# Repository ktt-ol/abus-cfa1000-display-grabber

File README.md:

# ABUS CFA1000 Display Grabber

This project's aim is accessing information from the ABUS CFA1000,
that are only shown on its display. For this task the display is
removed and the display pins are connected to a custom PCB developed
in this repository.

You can find more details here:

https://www.mainframe.io/project/abus-cfa1000-display-grabber.html

The PCB has been developed with KiCAD 4.0, which is available from
kicad-pcb.org for all major operating systems.

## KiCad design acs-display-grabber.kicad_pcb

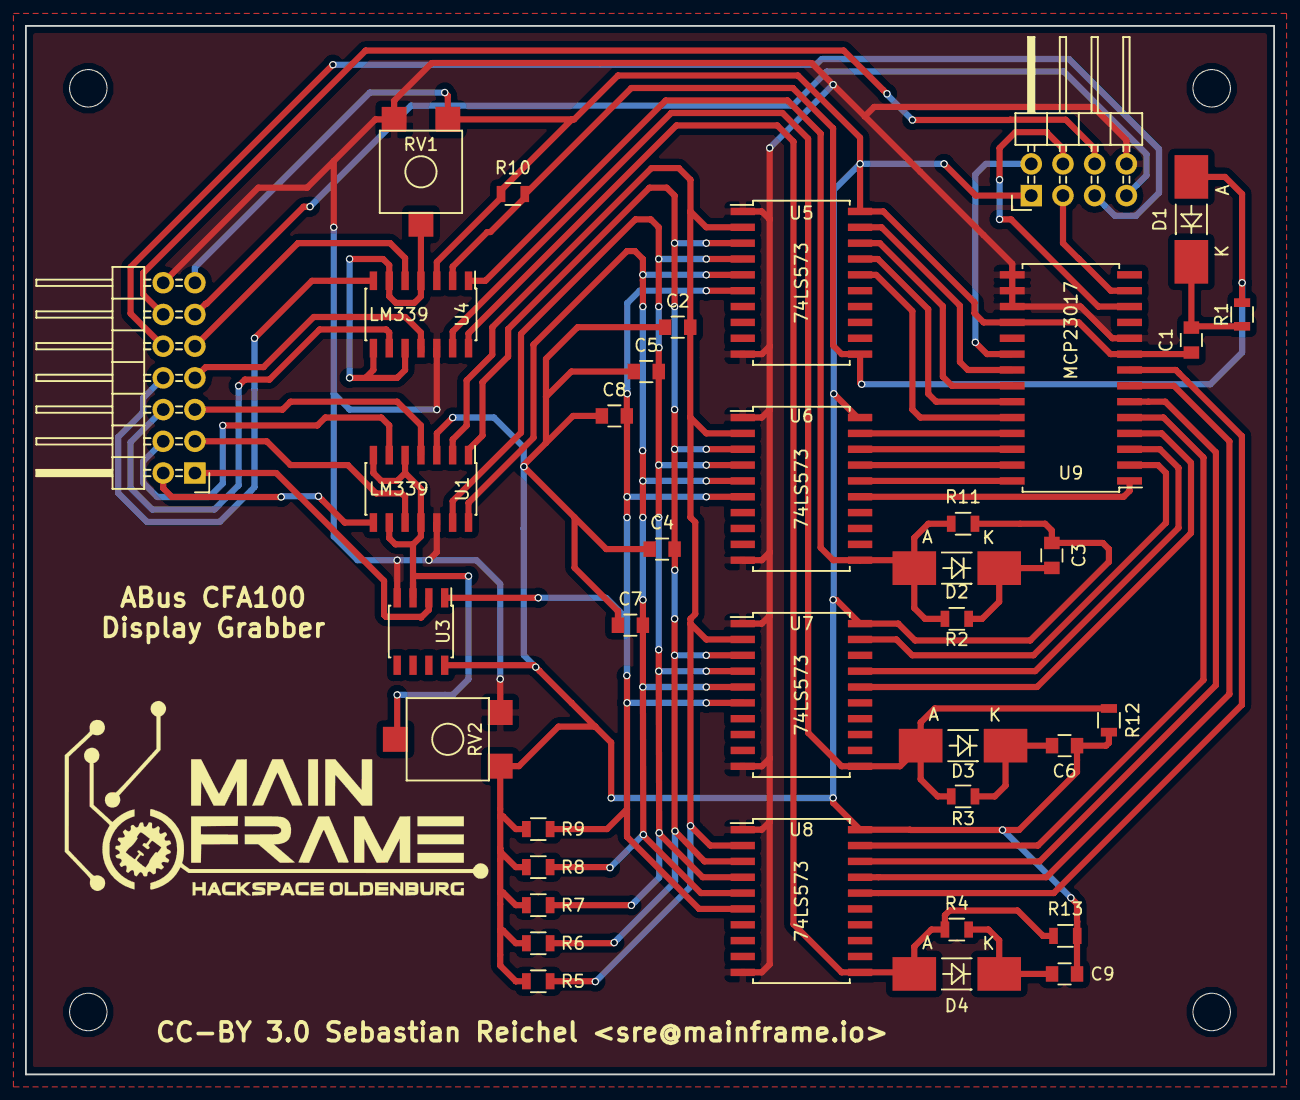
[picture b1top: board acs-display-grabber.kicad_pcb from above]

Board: 2 copper layers, 100.0 x 84.0 mm, 38 parts (0 on the bottom side), 48 nets.

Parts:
C1, C3, C6, C9: 20nF; C_0805
C2, C4, C5, C7, C8: 10nF; C_0805
D1, D2, D3, D4: 1N4007; MELF_Handsoldering
P1: CONN_02X07; Pin_Header_Angled_2x07
P2: CONN_02X04; Pin_Header_Angled_2x04
R1, R2, R3, R4: 1.8K; R_0805
R5, R6, R7, R8, R9, R10, R11, R12, R13: 3.3K; R_0805
RV1, RV2: POT; ACP_CA6
U1, U4: LM339; SOIC-14_3.9x8.7mm_Pitch1.27mm
U3: LM393; SOIC-8_3.9x4.9mm_Pitch1.27mm
U5, U6, U7, U8: 74LS573; SOIC-20_7.5x12.8mm_Pitch1.27mm
U9: MCP23017; SOIC-28_7.5x17.9mm_Pitch1.27mm

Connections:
+5V: C1.2, C2.1, C3.2, C4.1, C5.1, C6.2, C7.1, C8.1, C9.2, P1.13, P2.1, R5.1, R6.1, R7.1, R8.1, R9.1, R10.1, R11.1, R12.1, R13.1, RV1.1, RV2.1, U1.3, U3.8, U4.3, U5.20, U6.20, U7.20, U8.20, U9.9, U9.18
/COM0: P1.9, U4.5
/COM0clean: D1.2, R1.1, R10.2, U4.2, U5.11
/COM1: P1.8, U4.7
/COM1clean: D2.2, R2.1, R11.2, U4.1, U6.11
/COM2: P1.7, U4.11
/COM2clean: D3.2, R3.1, R12.2, U4.13, U7.11
/COM3: P1.6, U4.9
/COM3clean: D4.2, R4.1, R13.2, U4.14, U8.11
/INT: P2.2, U9.20
/LOCK: P1.10, P2.5
/RESET: P1.11, P2.7
/SCL: P2.3, U9.13
/SDA: P2.4, U9.12
/SEG0: P1.5, U1.4
/SEG0clean: C2.2, R5.2, U1.2, U5.2, U6.2, U7.2, U8.2
/SEG1: P1.4, U1.6
/SEG1clean: C4.2, R6.2, U1.1, U5.3, U6.3, U7.3, U8.3
/SEG2: P1.3, U1.10
/SEG2clean: C5.2, R7.2, U1.13, U5.4, U6.4, U7.4, U8.4
/SEG3: P1.2, U1.8
/SEG3clean: C7.2, R8.2, U1.14, U5.5, U6.5, U7.5, U8.5
/SEG4: P1.1, U3.2
/SEG4clean: C8.2, R9.2, U3.1, U5.6, U6.6, U7.6, U8.6
/UNLOCK: P1.12, P2.6
/Vhigh: RV1.2, U4.4, U4.6, U4.8, U4.10
/Vlow: RV2.2, U1.5, U1.7, U1.9, U1.11, U3.3
GND: P1.14, P2.8, RV1.3, RV2.3, U1.12, U3.4, U4.12, U5.1, U5.10, U6.1, U6.10, U7.1, U7.10, U8.1, U8.10, U9.10, U9.15, U9.16, U9.17
unnamed: C1.1, D1.1, R1.2
unnamed: C3.1, D2.1, R2.2
unnamed: C6.1, D3.1, R3.2
unnamed: C9.1, D4.1, R4.2
unnamed: U5.16, U9.24
unnamed: U5.17, U9.23
unnamed: U5.18, U9.22
unnamed: U5.19, U9.21
unnamed: U6.15, U9.1
unnamed: U6.16, U9.28
unnamed: U6.17, U9.27
unnamed: U6.18, U9.26
unnamed: U6.19, U9.25
unnamed: U7.16, U9.4
unnamed: U7.17, U9.3
unnamed: U7.19, U9.2
unnamed: U8.16, U9.8
unnamed: U8.17, U9.7
unnamed: U8.18, U9.6
unnamed: U8.19, U9.5

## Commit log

2016-12-10 version 1
2016-12-10 version 2
2016-12-10 version 3
2016-12-10 add README

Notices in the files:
acs-display-grabber.kicad_pcb:
CC-BY 3.0 Sebastian Reichel
